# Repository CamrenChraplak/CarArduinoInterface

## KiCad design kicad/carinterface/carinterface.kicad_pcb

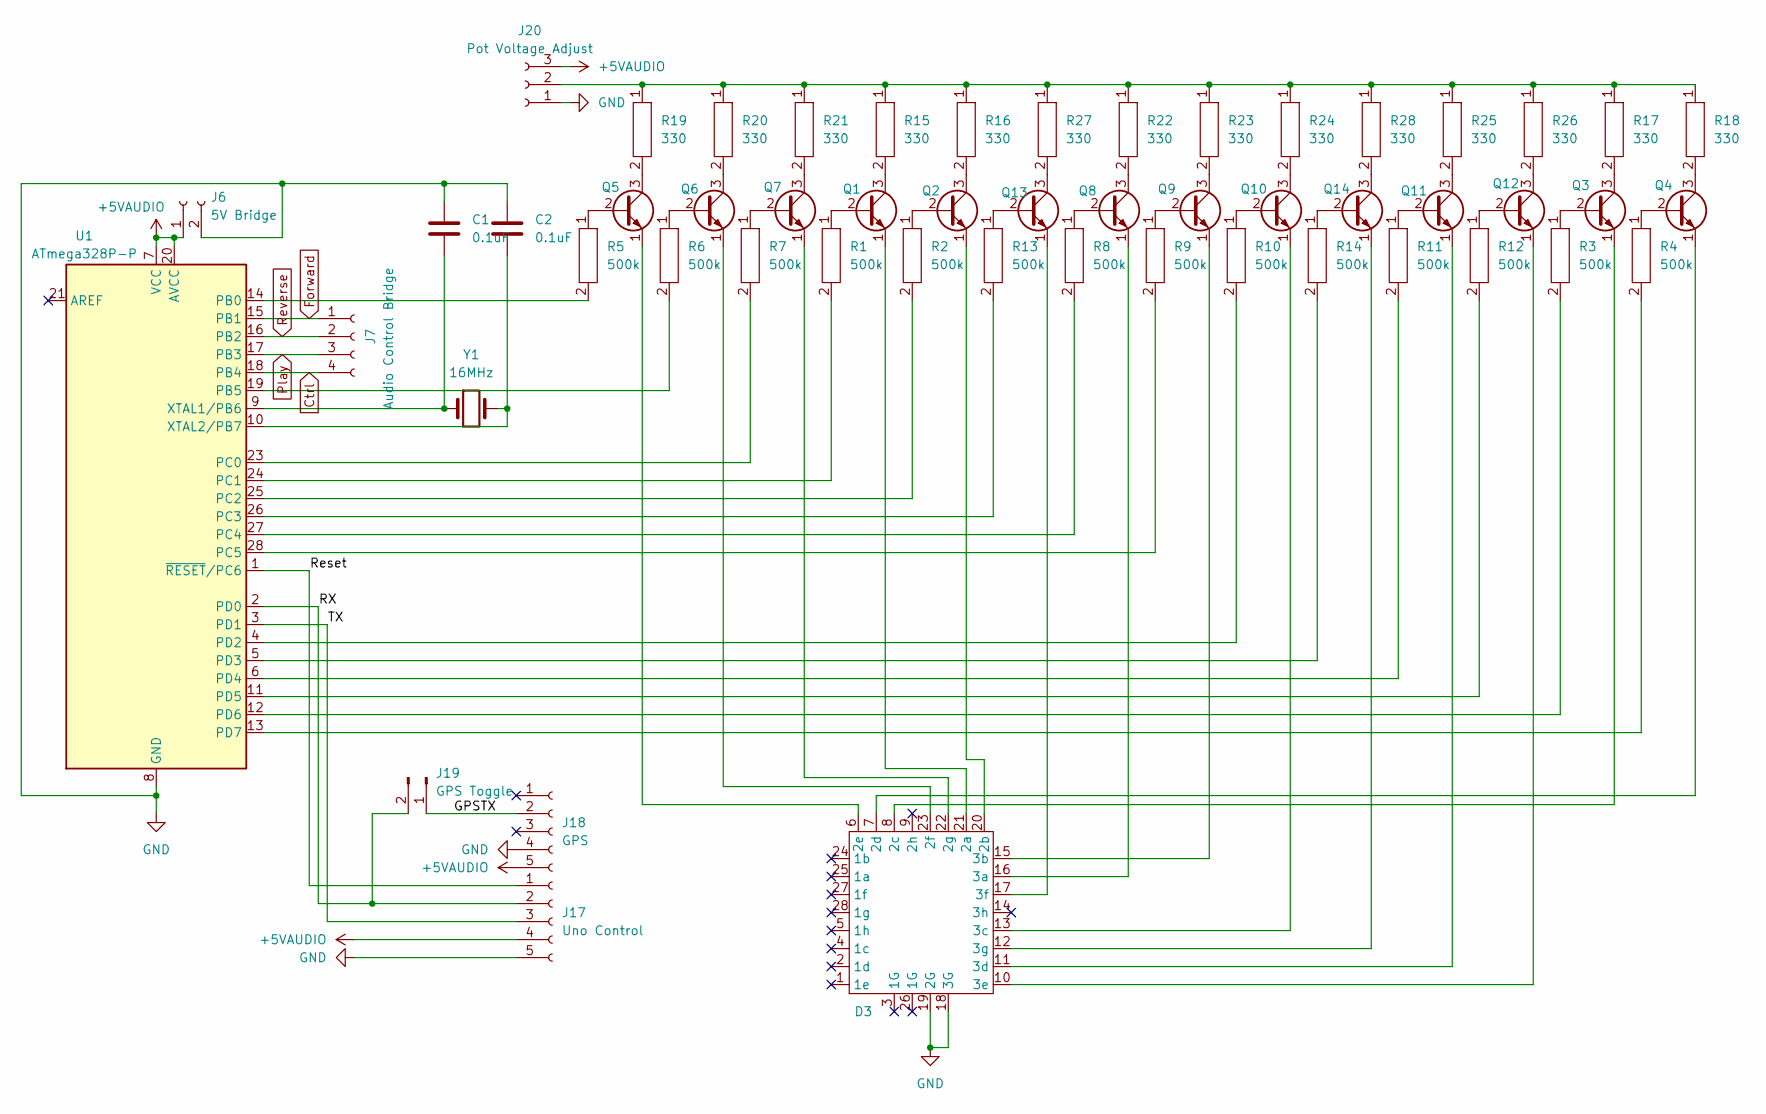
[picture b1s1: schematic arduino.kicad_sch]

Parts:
C1, C2: 0.1uF; C_Disc_D3.0mm_W1.6mm_P2.50mm
D3: Kingbright 3 Digit Common Cathode
J6: 5V Bridge; PinSocket_1x02_P2.54mm_Vertical
J7: Audio Control Bridge; PinSocket_1x04_P2.54mm_Vertical
J17: Uno Control; PinSocket_1x05_P2.54mm_Vertical
J18: GPS; PinSocket_1x05_P2.54mm_Vertical
J19: GPS Toggle; PinHeader_1x02_P2.54mm_Vertical
J20: Pot Voltage Adjust; PinSocket_1x03_P2.54mm_Vertical
Q1, Q2, Q3, Q4, Q5, Q6, Q7, Q8, Q9, Q10, Q11, Q12, Q13, Q14: BC107; TO-18-3
R1, R2, R3, R4, R5, R6, R7, R8, R9, R10, R11, R12, R13, R14: 500k; Vertical Resistor
R15, R16, R17, R18, R19, R20, R21, R22, R23, R24, R25, R26, R27, R28: 330; Vertical Resistor
U1: ATmega328P-P; DIP-28_W7.62mm
Y1: 16MHz; Crystal_HC18-U_Vertical

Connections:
+5VAUDIO: J6.1, J17.4, J18.5, J20.3, U1.7 (VCC), U1.20 (AVCC); also elsewhere on the board
/Arduino/GPSTX: J18.2, J19.1
/Arduino/RX: J17.2, J19.2, U1.2 (PD0)
/Arduino/Reset: J17.1, U1.1 (~RESET/PC6)
/Arduino/TX: J17.3, U1.3 (PD1)
Ctrl: J7.4, U1.18 (PB4); also elsewhere on the board
Forward: J7.1, U1.15 (PB1); also elsewhere on the board
GND: C1.1, C2.2, D3.18 (3G), D3.19 (2G), J6.2, J17.5, J18.4, J20.1, U1.8 (GND), U1.22 (GND); also elsewhere on the board
unnamed: D3.21 (2a), Q1.1 (E)
unnamed: D3.20 (2b), Q2.1 (E)
unnamed: D3.8 (2c), Q3.1 (E)
unnamed: D3.7 (2d), Q4.1 (E)
unnamed: D3.6 (2e), Q5.1 (E)
unnamed: D3.23 (2f), Q6.1 (E)
unnamed: D3.22 (2g), Q7.1 (E)
unnamed: D3.16 (3a), Q8.1 (E)
unnamed: D3.15 (3b), Q9.1 (E)
unnamed: D3.13 (3c), Q10.1 (E)
unnamed: D3.11 (3d), Q11.1 (E)
unnamed: D3.10 (3e), Q12.1 (E)
unnamed: D3.17 (3f), Q13.1 (E)
unnamed: D3.12 (3g), Q14.1 (E)
unnamed: J20.2, R15.1, R16.1, R17.1, R18.1, R19.1, R20.1, R21.1, R22.1, R23.1, R24.1, R25.1, R26.1, R27.1, R28.1
unnamed: Q1.2 (B), R1.1
unnamed: Q1.3 (C), R15.2
unnamed: Q2.2 (B), R2.1
unnamed: Q2.3 (C), R16.2
unnamed: Q3.2 (B), R3.1
unnamed: Q3.3 (C), R17.2
unnamed: Q4.2 (B), R4.1
unnamed: Q4.3 (C), R18.2
unnamed: Q5.2 (B), R5.1
unnamed: Q5.3 (C), R19.2
unnamed: Q6.2 (B), R6.1
unnamed: Q6.3 (C), R20.2
unnamed: Q7.2 (B), R7.1
unnamed: Q7.3 (C), R21.2
unnamed: Q8.2 (B), R8.1
unnamed: Q8.3 (C), R22.2
unnamed: Q9.2 (B), R9.1
unnamed: Q9.3 (C), R23.2
unnamed: Q10.2 (B), R10.1
unnamed: Q10.3 (C), R24.2
unnamed: Q11.2 (B), R11.1
unnamed: Q11.3 (C), R25.2
unnamed: Q12.2 (B), R12.1
unnamed: Q12.3 (C), R26.2
unnamed: Q13.2 (B), R13.1
unnamed: Q13.3 (C), R27.2
unnamed: Q14.2 (B), R14.1
unnamed: Q14.3 (C), R28.2
unnamed: R5.2, U1.14 (PB0)
unnamed: R6.2, U1.19 (PB5)
unnamed: R7.2, U1.23 (PC0)
unnamed: R1.2, U1.24 (PC1)
unnamed: R2.2, U1.25 (PC2)
unnamed: R13.2, U1.26 (PC3)
unnamed: R8.2, U1.27 (PC4)
unnamed: R9.2, U1.28 (PC5)
unnamed: R10.2, U1.4 (PD2)
unnamed: R14.2, U1.5 (PD3)
unnamed: R11.2, U1.6 (PD4)
unnamed: R12.2, U1.11 (PD5)
unnamed: R3.2, U1.12 (PD6)
unnamed: R4.2, U1.13 (PD7)
unnamed: C1.2, U1.9 (XTAL1/PB6), Y1.1
unnamed: C2.1, U1.10 (XTAL2/PB7), Y1.2
Play: J7.3, U1.17 (PB3); also elsewhere on the board
Reverse: J7.2, U1.16 (PB2); also elsewhere on the board

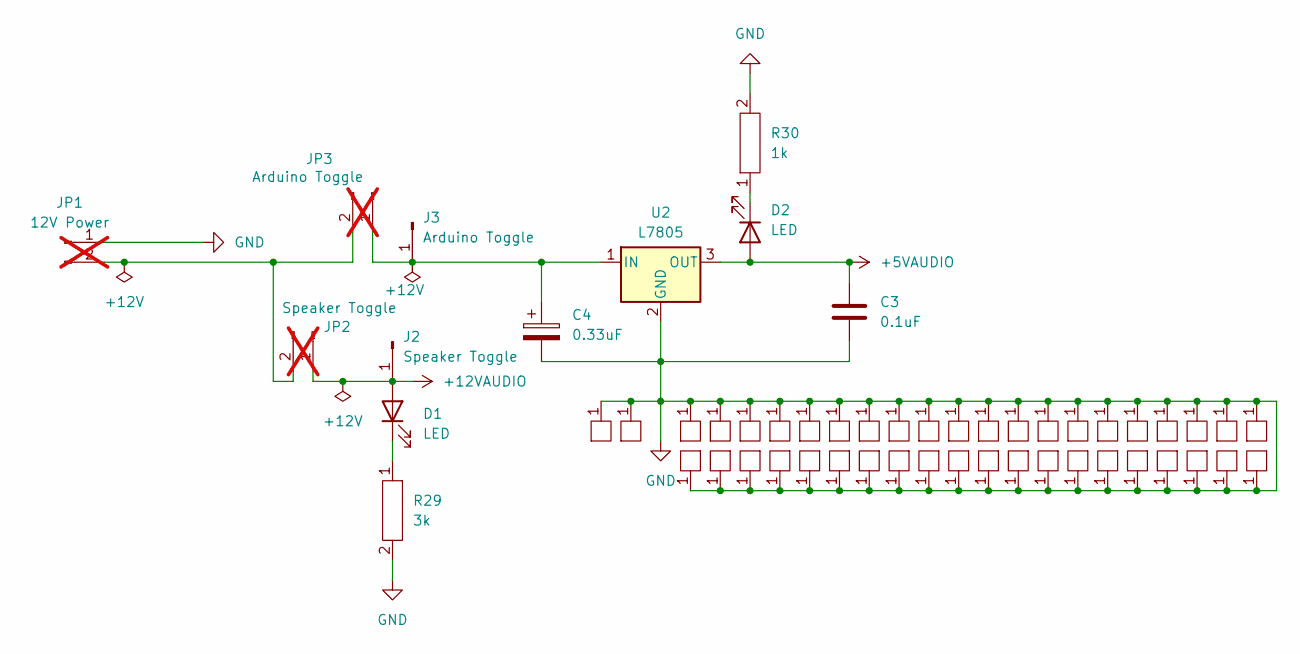
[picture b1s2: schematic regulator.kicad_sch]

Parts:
C3: 0.1uF; C_Disc_D3.0mm_W1.6mm_P2.50mm
C4: 0.33uF; CP_Radial_D5.0mm_P2.00mm
D1, D2: LED; LED_D3.0mm
J2: Speaker Toggle; SolderWire-0.75sqmm_1x01_D1.25mm_OD2.3mm
J3: Arduino Toggle; SolderWire-0.75sqmm_1x01_D1.25mm_OD2.3mm
JP1: 12V Power; SolderWire-1sqmm_1x02_P5.4mm_D1.4mm_OD2.7mm; not fitted
JP2: Speaker Toggle; SolderWire-1sqmm_1x02_P5.4mm_D1.4mm_OD2.7mm; not fitted
JP3: Arduino Toggle; SolderWire-1sqmm_1x02_P5.4mm_D1.4mm_OD2.7mm; not fitted
R29: 3k; Vertical Resistor
R30: 1k; Vertical Resistor
T1, T2: Thermal Pad
T3, T4, T5, T6, T7, T8, T9, T10, T11, T12, T13, T14, T15, T16, T17, T18, T19, T20, T21, T22, T23, T24, T25, T26, T27, T28, T29, T30, T31, T32, T33, T34, T35, T36, T37, T38, T39, T40, T41, T42: smallthermalpad
U2: L7805; TO-220-3_Vertical

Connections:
+5VAUDIO: C3.1, D2.2 (A), U2.3 (OUT); also elsewhere on the board
+12VAUDIO: D1.2 (A), J2.1, JP2.1
GND: C3.2, C4.2, JP1.1, R29.2, R30.2, T1.1 (Sink), T2.1 (Sink), T3.1 (Pad), T4.1 (Pad), T5.1 (Pad), T6.1 (Pad), T7.1 (Pad), T8.1 (Pad), T9.1 (Pad), T10.1 (Pad), T11.1 (Pad), T12.1 (Pad), T13.1 (Pad), T14.1 (Pad), T15.1 (Pad), T16.1 (Pad), T17.1 (Pad), T18.1 (Pad), T19.1 (Pad), T20.1 (Pad), T21.1 (Pad), T22.1 (Pad), T23.1 (Pad), T24.1 (Pad), T25.1 (Pad), T26.1 (Pad), T27.1 (Pad), T28.1 (Pad), T29.1 (Pad), T30.1 (Pad), T31.1 (Pad), T32.1 (Pad), T33.1 (Pad), T34.1 (Pad), T35.1 (Pad), T36.1 (Pad), T37.1 (Pad), T38.1 (Pad), T39.1 (Pad), T40.1 (Pad), T41.1 (Pad), T42.1 (Pad), U2.2 (GND); also elsewhere on the board
unnamed: D1.1 (K), R29.1
unnamed: D2.1 (K), R30.1
unnamed: C4.1, J3.1, JP3.1, U2.1 (IN)
unnamed: JP1.2, JP2.2, JP3.2

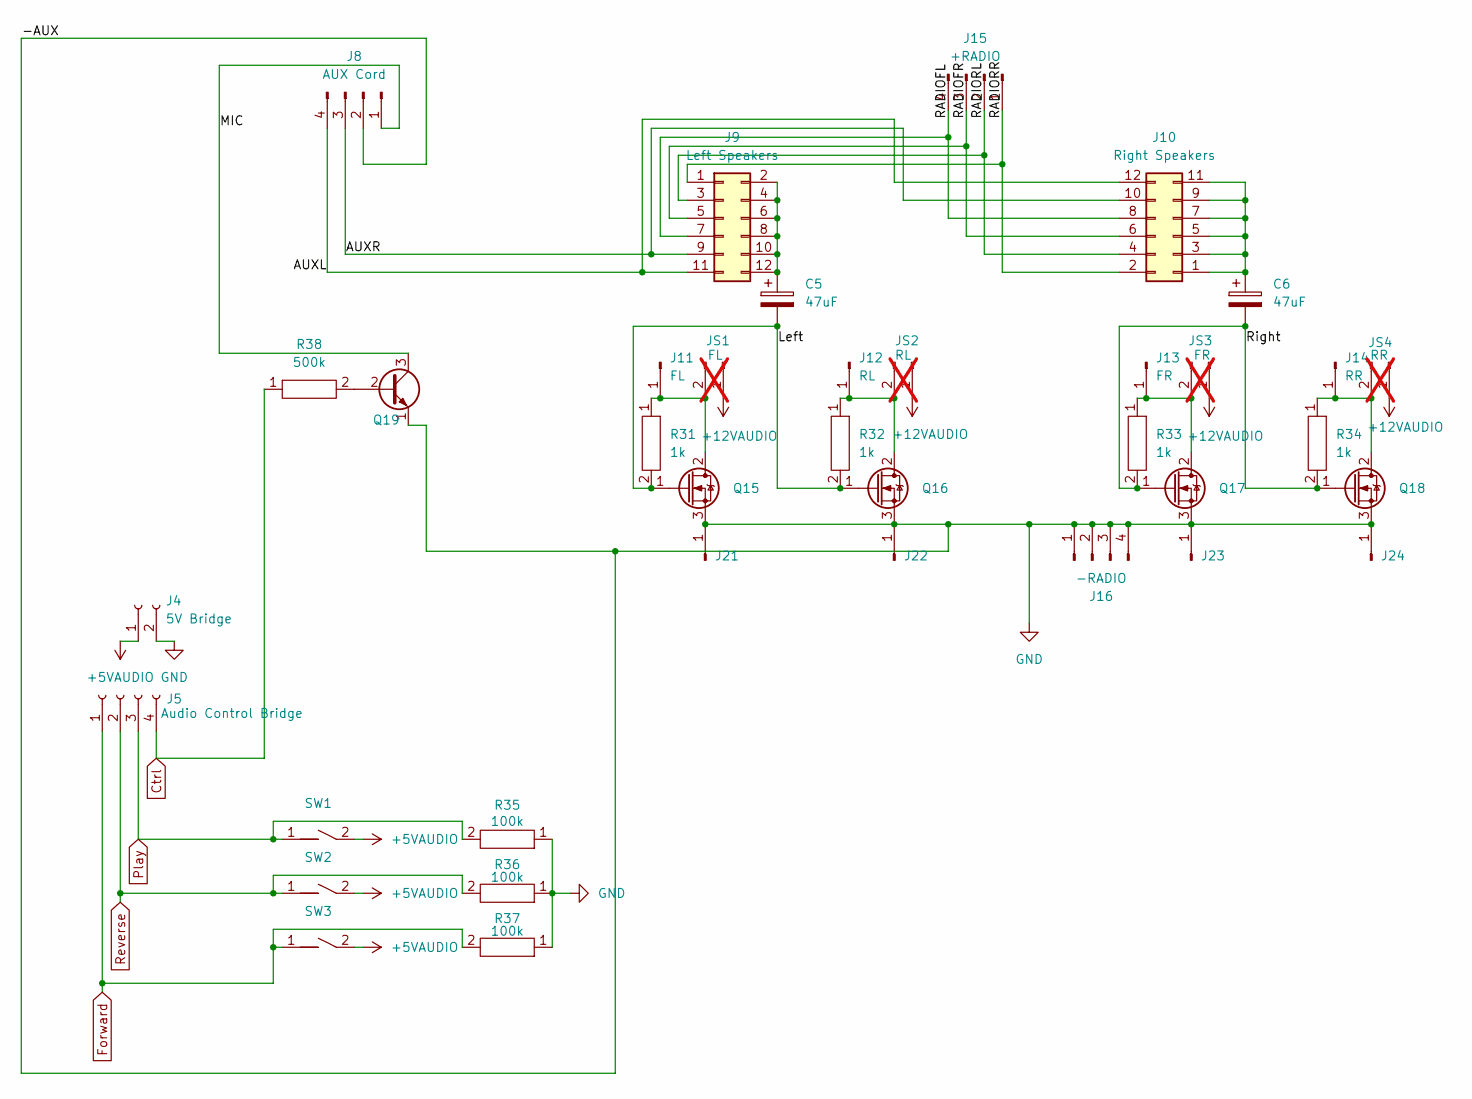
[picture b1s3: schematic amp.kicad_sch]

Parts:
C5, C6: 47uF; CP_Radial_D6.3mm_P2.50mm
J4: 5V Bridge; PinSocket_1x02_P2.54mm_Vertical
J5: Audio Control Bridge; PinSocket_1x04_P2.54mm_Vertical
J8: AUX Cord; SolderWire-0.5sqmm_1x04_P4.6mm_D0.9mm_OD2.1mm
J9: Left Speakers; PinHeader_2x06_P2.54mm_Vertical
J10: Right Speakers; PinHeader_2x06_P2.54mm_Vertical
J11: FL; SolderWire-0.75sqmm_1x01_D1.25mm_OD2.3mm
J12: RL; SolderWire-0.75sqmm_1x01_D1.25mm_OD2.3mm
J13: FR; SolderWire-0.75sqmm_1x01_D1.25mm_OD2.3mm
J14: RR; SolderWire-0.75sqmm_1x01_D1.25mm_OD2.3mm
J15: +RADIO; SolderWire-0.5sqmm_1x04_P4.6mm_D0.9mm_OD2.1mm
J16: -RADIO; SolderWire-0.5sqmm_1x04_P4.6mm_D0.9mm_OD2.1mm
J21, J22, J23, J24: Conn_01x01_Pin; SolderWire-0.75sqmm_1x01_D1.25mm_OD2.3mm
JS1: FL; SolderWire-1sqmm_1x02_P5.4mm_D1.4mm_OD2.7mm; not fitted
JS2: RL; SolderWire-1sqmm_1x02_P5.4mm_D1.4mm_OD2.7mm; not fitted
JS3: FR; SolderWire-1sqmm_1x02_P5.4mm_D1.4mm_OD2.7mm; not fitted
JS4: RR; SolderWire-1sqmm_1x02_P5.4mm_D1.4mm_OD2.7mm; not fitted
Q15, Q16, Q17, Q18: DN2540N5-G; TO-220-3_Vertical
Q19: BC107; TO-18-3
R31, R32, R33, R34: 1k; Vertical Resistor
R35, R36, R37: 100k; Vertical Resistor
R38: 500k; Vertical Resistor
SW1, SW2, SW3: pushbutton

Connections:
+5VAUDIO: J4.1, SW1.2, SW2.2, SW3.2; also elsewhere on the board
/Amp/AUXL: J8.4, J9.11, J10.12
/Amp/AUXR: J8.3, J9.9, J10.10
/Amp/Left: C5.2, Q15.1 (G), Q16.1 (G), R31.2, R32.2
/Amp/MIC: J8.1, Q19.3 (C)
/Amp/RADIOFL: J9.7, J10.8, J15.4
/Amp/RADIOFR: J9.5, J10.6, J15.3
/Amp/RADIORL: J9.3, J10.4, J15.2
/Amp/RADIORR: J9.1, J10.2, J15.1
/Amp/Right: C6.2, Q17.1 (G), Q18.1 (G), R33.2, R34.2
Ctrl: J5.4, R38.1; also elsewhere on the board
Forward: J5.1, R37.2, SW3.1; also elsewhere on the board
GND: J4.2, J8.2, J16.1, J16.2, J16.3, J16.4, J21.1, J22.1, J23.1, J24.1, Q15.3 (S), Q16.3 (S), Q17.3 (S), Q18.3 (S), Q19.1 (E), R35.1, R36.1, R37.1; also elsewhere on the board
unnamed: C5.1, J9.2, J9.4, J9.6, J9.8, J9.10, J9.12
unnamed: C6.1, J10.1, J10.3, J10.5, J10.7, J10.9, J10.11
unnamed: J11.1, JS1.2, Q15.2 (D), R31.1
unnamed: J12.1, JS2.2, Q16.2 (D), R32.1
unnamed: J13.1, JS3.2, Q17.2 (D), R33.1
unnamed: J14.1, JS4.2, Q18.2 (D), R34.1
unnamed: JS1.1, JS2.1, JS3.1, JS4.1
unnamed: Q19.2 (B), R38.2
Play: J5.3, R35.2, SW1.1; also elsewhere on the board
Reverse: J5.2, R36.2, SW2.1; also elsewhere on the board

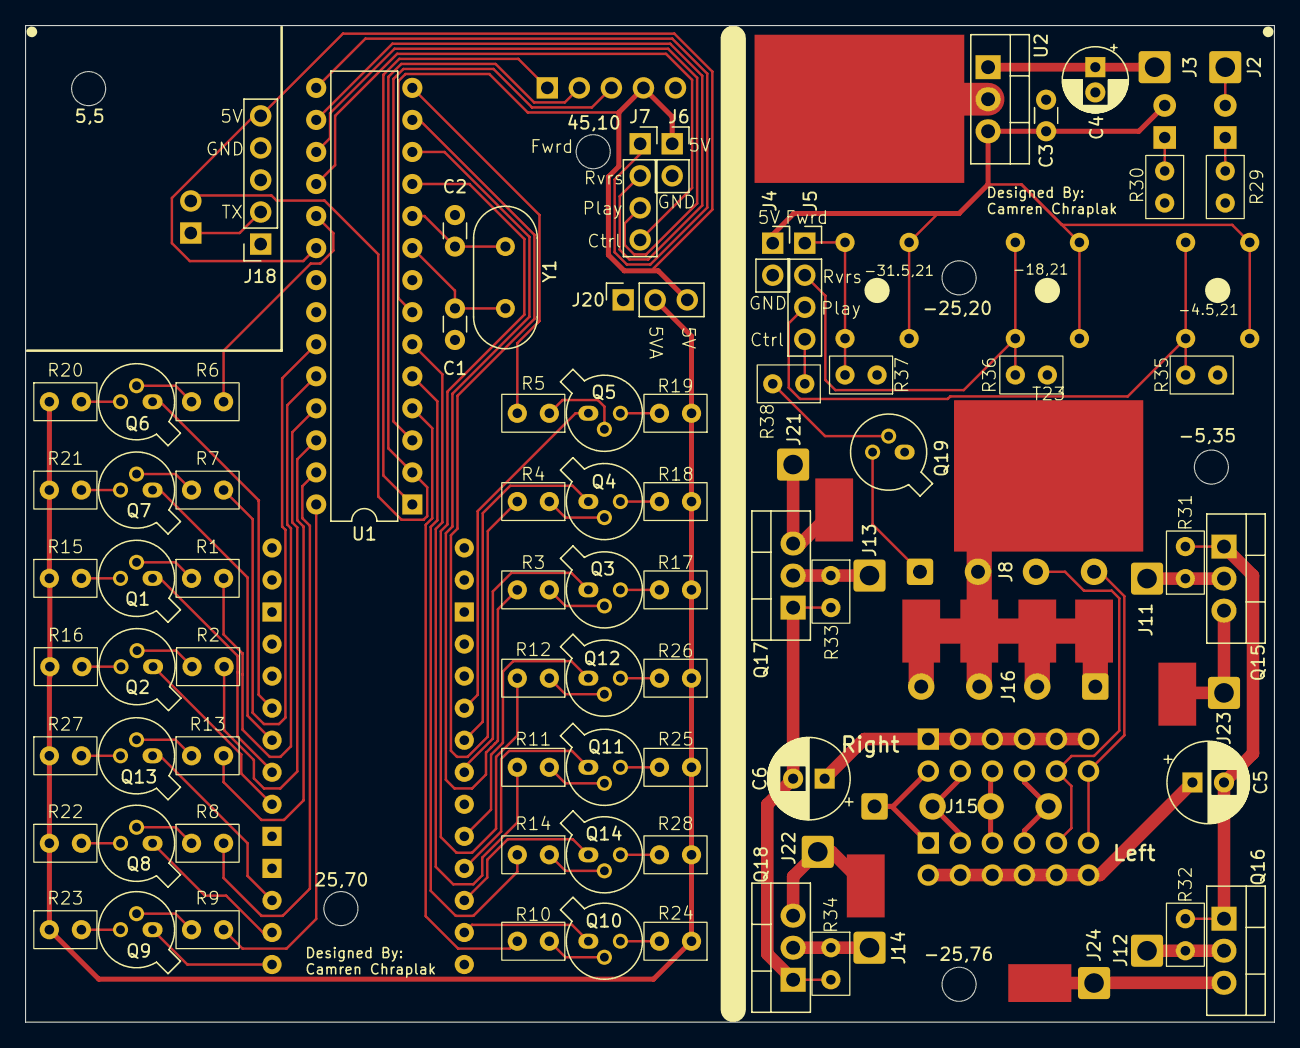
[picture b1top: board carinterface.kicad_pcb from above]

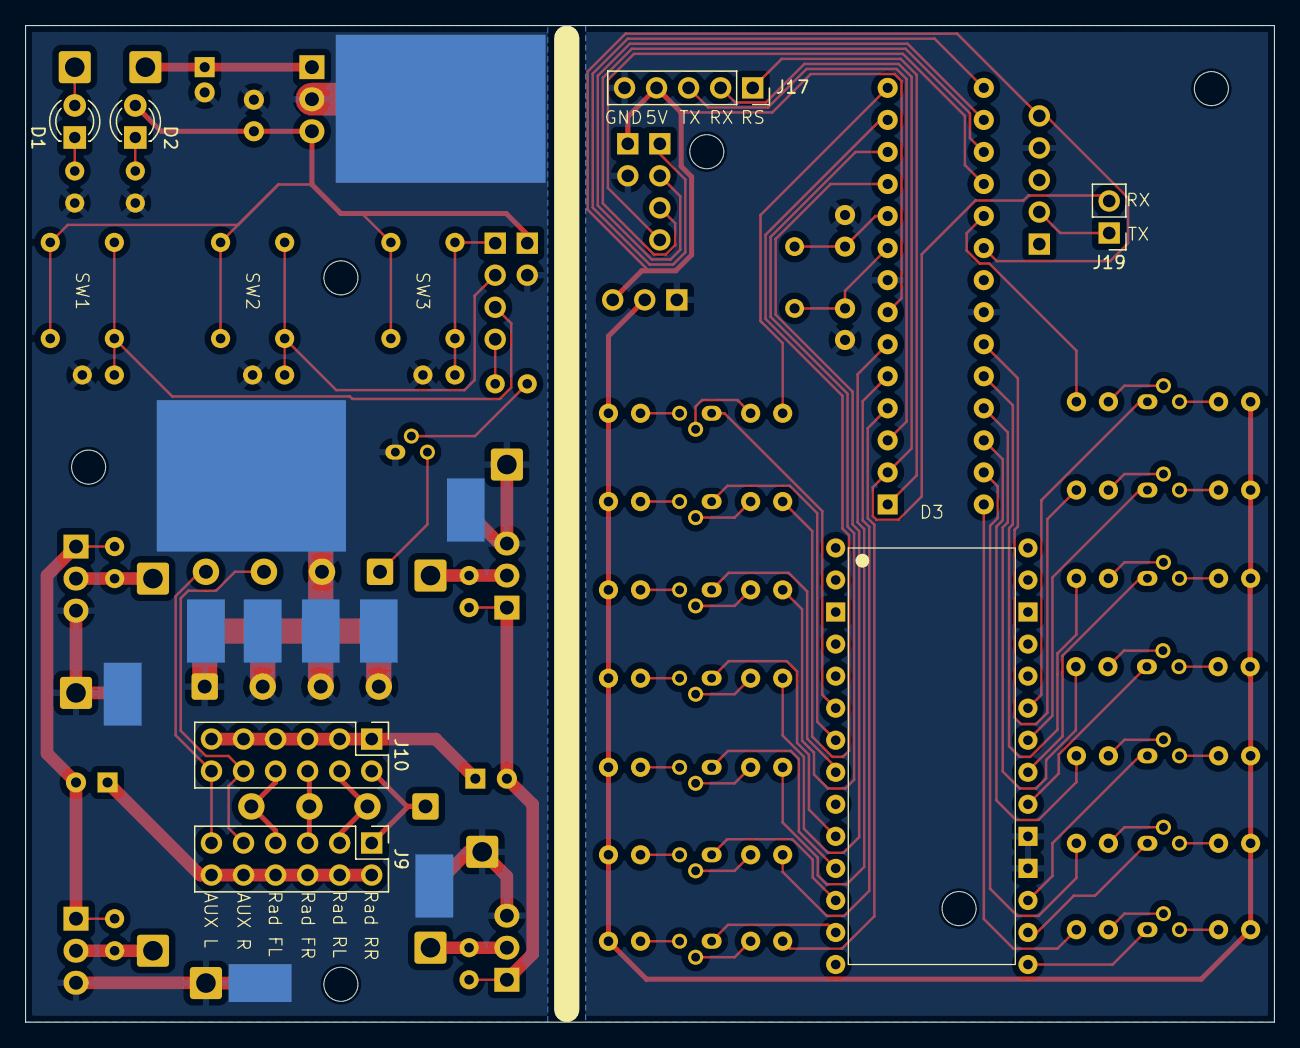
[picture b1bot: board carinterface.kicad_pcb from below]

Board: 2 copper layers, 99.0 x 79.0 mm, 137 parts (31 on the bottom side), 89 nets.

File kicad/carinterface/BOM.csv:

"Id";"Designator";"Footprint";"Quantity";"Designation";"Supplier and ref";
1;"R32,R30,R34,R33,R31";"Vertical Resistor";5;"1k";;;
2;"J11";"SolderWire-0.75sqmm_1x01_D1.25mm_OD2.3mm";1;"FL";;;
3;"Q15,Q16,Q18,Q17";"TO-220-3_Vertical";4;"DN2540N5-G";;;
4;"J15";"SolderWire-0.5sqmm_1x04_P4.6mm_D0.9mm_OD2.1mm";1;"+RADIO";;;
5;"Q7,Q4,Q2,Q14,Q1,Q19,Q5,Q3,Q8,Q9,Q11,Q6,Q13,Q10,Q12";"TO-18-3";15;"BC107";;;
6;"R14,R4,R7,R8,R10,R12,R5,R38,R11,R3,R9,R6,R13,R2,R1";"Vertical Resistor";15;"500k";;;
7;"R23,R24,R27,R22,R21,R28,R17,R25,R20,R19,R15,R18,R16,R26";"Vertical Resistor";14;"330";;;
8;"J6,J4";"PinSocket_1x02_P2.54mm_Vertical";2;"5V Bridge";;;
9;"R29";"Vertical Resistor";1;"3k";;;
10;"C3,C2,C1";"C_Disc_D3.0mm_W1.6mm_P2.50mm";3;"0.1uF";;;
11;"J2";"SolderWire-1sqmm_1x02_P5.4mm_D1.4mm_OD2.7mm";1;"Speaker Toggle";;;
12;",,,,,";"";6;"";;;
13;"R36,R37,R35";"Vertical Resistor";3;"100k";;;
14;"C4";"CP_Radial_D5.0mm_P2.00mm";1;"0.33uF";;;
15;"U2";"TO-220-3_Vertical";1;"L7805";;;
16;"U1";"DIP-28_W7.62mm";1;"ATmega328P-P";;;
17;"J23,J21,J22,J24";"SolderWire-0.75sqmm_1x01_D1.25mm_OD2.3mm";4;"Conn_01x01_Pin";;;
18;"C6,C5";"CP_Radial_D6.3mm_P2.50mm";2;"47uF";;;
19;"J20";"PinSocket_1x03_P2.54mm_Vertical";1;"Pot Voltage Adjust";;;
20;"D1,D2";"LED_D3.0mm";2;"LED";;;
21;"J8";"SolderWire-0.5sqmm_1x04_P4.6mm_D0.9mm_OD2.1mm";1;"AUX Cord";;;
22;"J13";"SolderWire-0.75sqmm_1x01_D1.25mm_OD2.3mm";1;"FR";;;
23;"J5,J7";"PinSocket_1x04_P2.54mm_Vertical";2;"Audio Control Bridge";;;
24;"J18";"PinSocket_1x05_P2.54mm_Vertical";1;"GPS";;;
25;"J14";"SolderWire-0.75sqmm_1x01_D1.25mm_OD2.3mm";1;"RR";;;
26;"J1";"SolderWire-1sqmm_1x02_P5.4mm_D1.4mm_OD2.7mm";1;"12V Power";;;
27;"Y1";"Crystal_HC18-U_Vertical";1;"16MHz";;;
28;"J3";"SolderWire-1sqmm_1x02_P5.4mm_D1.4mm_OD2.7mm";1;"Arduino Toggle";;;
29;"J12";"SolderWire-0.75sqmm_1x01_D1.25mm_OD2.3mm";1;"RL";;;
30;"J16";"SolderWire-0.5sqmm_1x04_P4.6mm_D0.9mm_OD2.1mm";1;"-RADIO";;;
31;"J9";"PinHeader_2x06_P2.54mm_Vertical";1;"Left Speakers";;;
32;"SW3,SW1,SW2";"pushbutton";3;"~";;;
33;"J10";"PinHeader_2x06_P2.54mm_Vertical";1;"Right Speakers";;;
34;"D3";"Kingbright 3 Digit Common Cathode";1;"~";;;
35;"J17";"PinSocket_1x05_P2.54mm_Vertical";1;"Uno Control";;;
36;"J19";"PinHeader_1x02_P2.54mm_Vertical";1;"GPS Toggle";;;

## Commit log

2024-10-21 Added local files
